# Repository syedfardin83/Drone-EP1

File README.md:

##  LOS (Lark OS):
LOS is a firmware specifically built for the drone flight controller Lark1.

It inludes:
- Reading desired angles/rates from the in-built bluetooth on the ESP32.
- Reading the IMU data (MPU6050).
- Using a complementary filter to obtain the current angles of the drone.
- A PID loop to maintain stability and a smooth flight.

### LOS 1.0
A super loop firmware, with only 1dof control (throttle coontrol only). It was built to test basic tasks like Bluetooth reading, commands string formatting, and motor PWM outputs. It does not include IMU reading and PID calculations.

It is tested and works well.

### LOS 1.1
It was supposed to be complete functional drone superloop firmware with 6dof. But, it did not function, due to some superloop firmware complications.

It is tested and does not work. Hence, moving on to LOS2 which will be FreeRTOS based.

### LOS 2.0
It is a FreeRTOS based complete drone firmware. It has two tasks.
- BT read task
- MPU read + PID calculation

As the Bluetooth task was in the same task in LOS1.1, it was causing the major lag, hence LOS2.0 separates the BT task, while the rest of the tasks are together in another task.

### LOS 2.1
It is an improverment over the LOS 2.0, which now includes 4 tasks.
- BT reading
- IMU reading
- Angles calculation - Complementary filter
- PID loop

LOS 2.1 is more robust, as it uses queues for intertransmission of data between tasks.

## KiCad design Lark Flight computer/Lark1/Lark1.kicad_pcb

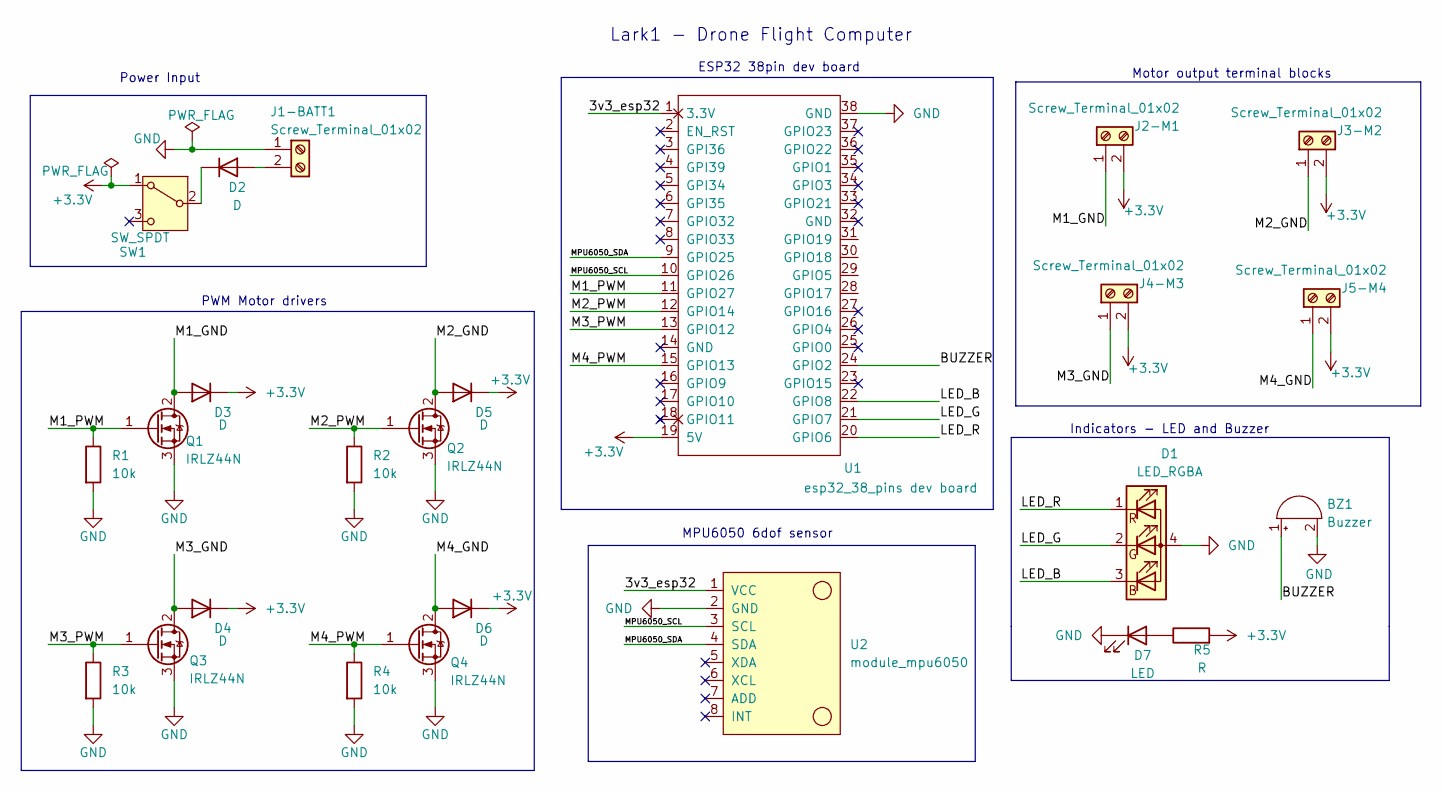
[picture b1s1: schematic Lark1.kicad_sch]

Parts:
BZ1: Buzzer; Buzzer_12x9.5RM7.6
D1: LED_RGBA; LED_D5.0mm-4_RGB_Wide_Pins
D2, D3, D4, D5, D6: D; D_5KPW_P12.70mm_Horizontal
D7: LED; LED_D3.0mm
J1-BATT1, J2-M1, J3-M2, J4-M3, J5-M4: Screw_Terminal_01x02; TerminalBlock_Altech_AK300-2_P5.00mm
Q1, Q2, Q3, Q4: IRLZ44N; TO-220-3_Vertical
R1, R2, R3, R4: 10k; R_Axial_DIN0204_L3.6mm_D1.6mm_P5.08mm_Horizontal
R5: R; R_Axial_DIN0204_L3.6mm_D1.6mm_P5.08mm_Horizontal
SW1: SW_SPDT; SW_Slide_SPDT_Angled_CK_OS102011MA1Q
U1: esp32_38_pins dev board; PinSocket_2x19_P2.54mm_Vertical
U2: module_mpu6050; PinSocket_1x08_P2.54mm_Vertical

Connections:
+3.3V: D3.1 (K), D4.1 (K), D5.1 (K), D6.1 (K), J2-M1.2, J3-M2.2, J4-M3.2, J5-M4.2, R5.2, SW1.1 (A), U1.19 (5V)
/3v3_esp32: U1.1 (3.3V), U2.1 (VCC)
/BUZZER: BZ1.1 (+), U1.24 (GPIO2)
/LED_B: D1.3 (BK), U1.22 (GPIO8)
/LED_G: D1.2 (GK), U1.21 (GPIO7)
/LED_R: D1.1 (RK), U1.20 (GPIO6)
/M1_GND: D3.2 (A), J2-M1.1, Q1.2 (D)
/M1_PWM: Q1.1 (G), R1.1, U1.11 (GPIO27)
/M2_GND: D5.2 (A), J3-M2.1, Q2.2 (D)
/M2_PWM: Q2.1 (G), R2.1, U1.12 (GPIO14)
/M3_GND: D4.2 (A), J4-M3.1, Q3.2 (D)
/M3_PWM: Q3.1 (G), R3.1, U1.13 (GPIO12)
/M4_GND: D6.2 (A), J5-M4.1, Q4.2 (D)
/M4_PWM: Q4.1 (G), R4.1, U1.15 (GPIO13)
/MPU6050_SCL: U1.10 (GPIO26), U2.3 (SCL)
/MPU6050_SDA: U1.9 (GPIO25), U2.4 (SDA)
GND: BZ1.2 (-), D1.4 (A), D7.1 (K), J1-BATT1.1, Q1.3 (S), Q2.3 (S), Q3.3 (S), Q4.3 (S), R1.2, R2.2, R3.2, R4.2, U1.38 (GND), U2.2 (GND)
unnamed: D2.2 (A), J1-BATT1.2
unnamed: D2.1 (K), SW1.2 (B)
unnamed: D7.2 (A), R5.1

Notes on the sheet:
Indicators - LED and Buzzer
PWM Motor drivers
Power Input
MPU6050 6dof sensor
Lark1 - Drone Flight Computer
ESP32 38pin dev board
Motor output terminal blocks

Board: 2 copper layers, 25 parts (0 on the bottom side), 20 nets, no tracks yet.

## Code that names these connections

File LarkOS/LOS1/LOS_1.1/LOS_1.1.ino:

//Lark OS 1.1
// six degrees of freedom (input from joystick)
// Main tasks:
// 1. Take bluetooth input
// 2. Read sensor data
// 3. Run PID

#include "BluetoothSerial.h"
#include <Arduino.h>
#include <Adafruit_MPU6050.h>
#include <Adafruit_Sensor.h>
#include <Wire.h>
#include <math.h>

// Software Objects
BluetoothSerial SerialBT;
Adafruit_MPU6050 mpu;

// Motor pins
int motor_pins[4] = {12,13,14,27};

// Sensor orientation
#define orientation 2

// Indicator Pins
#define LED_R_PIN NULL
#define LED_G_PIN 22
#define LED_B_PIN 23
#define BUZZER_PIN NULL

// MPU6050 pins
#define SCL_PIN 17
#define SDA_PIN 26

// Test button
#define BTN_PIN NULL

// Bluetooth name
#define bt_name "LOS 1.1"

// Serial reading variables
String inputString = "";
bool stringEnd = false;

// Drone control variables
double desiredAngles[3] = {0,0,0};
double throttleIncrement = 0;
double throttle = 0;
double currentAngles[3] = {0,0,0};
double* offsets;
double* data;
double integratedAngles[3] = {0,0,0};
double accAngles[3] = {0,0,0};
double alpha = 0.98;

// Time variables
unsigned long previous_time = 0;
unsigned long current_time = 0;
double dt;

// PID variables
double P=0.09,I=0.01,D=0.01;
double P_terms[3] = {0,0,0};
double I_terms[3] = {0,0,0};
double D_terms[3] = {0,0,0};
double current_errors[3] = {0,0,0};
double previous_errors[3] = {0,0,0};
double rate_outputs[3] = {0,0,0};

// Motor inputs
int motor_inputs[4] = {0,0,0,0};

double* getData(){
  /* Get new sensor events with the readings */
  sensors_event_t a, g, temp;
  mpu.getEvent(&a, &g, &temp);
  static double arr[6];
  arr[0] = a.acceleration.x;
  arr[1] = a.acceleration.y;
  arr[2] = a.acceleration.z;

  arr[3] = g.gyro.x;
  arr[4] = g.gyro.y;
  arr[5] = g.gyro.z;
  return arr;
  // AccX = a.acceleration.x
  // return [a.acceleration.x,a.acceleration.y,a.acceleration.z,a.gyro.x,a.gyro.y,a.gyro.z];
  // double data[6] = {a.acceleration.x, a.acceleration.y, a.acceleration.z, a.gyro.x, a.gyro.y, a.gyro.z};
}

double* getFilteredData(int n){
  double sums[6] = {0,0,0,0,0,0};

  static double avgs[6];

  //Finding sums
  for(int i=1; i<=n; i++){
    static double* data;
    data = getData();
    for(int j=0; j<6; j++){
      sums[j] = sums[j]+data[j];
    }
  }

  //Finding avgs
  for(int i=0; i<6; i++){
    avgs[i] = sums[i]/n;
  }

  return avgs;
}

double* calliberateSensor(){
  static double offsets[6];
  static double* data;
  data = getFilteredData(5);

  for(int i=0; i<6; i++){
    offsets[i] = data[i];
  }

  return offsets;
}

String* splitBySpace(String str){
  static String words[10];int i=0;String word = "";int wordIndex = 0;
  while(i<str.length()){
    if((str[i]==' ')){
      words[wordIndex] = word;
      word="";
      wordIndex++;i++;
      continue;
    }
    if(i==str.length()-1){
      word+=str[i];
      words[wordIndex] = word;break;
    }
    word+=str[i];
    i++;
  }
  return words;
}

void setup() {
  //Initialize all pins
  for(int i=0;i<4;i++){
    pinMode(motor_pins[i],OUTPUT);
  }

  // pinMode(LED_R_PIN,OUTPUT);
  pinMode(LED_G_PIN,OUTPUT);
  pinMode(LED_B_PIN,OUTPUT);
  pinMode(BUZZER_PIN,OUTPUT);

  pinMode(BTN_PIN,INPUT);

  //Initialize Serial
  SerialBT.begin(bt_name);
  Serial.begin(115200);
  delay(100);

  //Initialize MPU6050
  Wire.begin(SDA_PIN,SCL_PIN);
  if (!mpu.begin()) {
    Serial.println("Failed to find MPU6050 chip");
    while (1) {
      delay(10);
    }
  }
  mpu.setAccelerometerRange(MPU6050_RANGE_16_G);
  mpu.setGyroRange(MPU6050_RANGE_250_DEG);
  mpu.setFilterBandwidth(MPU6050_BAND_21_HZ);
  delay(100);

  //Calliberate sensor
  offsets = calliberateSensor();
}

void loop() {

  //Bluetooth read
  if(SerialBT.available()){
    char ch = SerialBT.read();
    if (ch == '\n') {
      stringEnd = true;
    } else {
      inputString += ch;
    }
  }
  if(stringEnd){
        inputString.trim();
        if(inputString=="STOP"){
          Serial.println("Emergency stop protocol initiated !!!");
          for(int i=0;i<4;i++){
            analogWrite(motor_pins[i],0);
          }
          while(1){

          }
        }
        Serial.println(inputString);
        String* command = splitBySpace(inputString);

        //Update desired angles
        for(int i=0;i<3;i++){
          desiredAngles[i] = radians(command[i].toDouble());
        }
        throttleIncrement = command[3].toDouble();
        throttle+=throttleIncrement;
        throttleIncrement = 0;

        inputString = "";
        stringEnd = false;

        // Serial.print(throttle);
        // Serial.print("  ");
        // for(int i=0;i<3;i++){
        //   Serial.print(desiredAngles[i]);
        //   Serial.print("  ");
        }
        // Serial.println("");


  // Read Sensor data
    // current_time = micros();
    // data = getFilteredData(5);


    // // Calculate angles
    // dt = (current_time-previous_time)*pow(10,-6);
    // //Integrated Angles
    // for(int i=0;i<3;i++){
    //   integratedAngles[i]+=dt*(data[i+3]-offsets[i+3]);
    // }

    // //Angles from triginometry/Acceletration
    // if(orientation == 2){
    //   if(data[0]==0){
    //     accAngles[1] = 3.14/2;
    //     accAngles[2] = 3.14/2;
    //   }else{
    //         accAngles[2] = atan(data[1]/data[0]);
    //         accAngles[1] = atan(data[2]/data[0]);
    //   }
    // }
    // //Sign correction
    // if(orientation==2){
    //   // double temp=integratedAngles[0];
    //   accAngles[2] = -accAngles[2];
    //   // integratedAngles[0] = -temp;
    // }
    // // accAngles[0] = integratedAngles[0];
    // // //Complementary filter
    // for(int i=1; i<3; i++){
    //   currentAngles[i] = alpha*integratedAngles[i] + (1-alpha)*accAngles[i];
    // }
    // currentAngles[0] = integratedAngles[0];

    // // PID control


    // // Finding errors in angles
    // for(int i =0;i<3;i++){
    //   current_errors[i] = currentAngles[i]-desiredAngles[i];
    // }

    // // // Find rate outputs:
    // for(int i=0;i<3;i++){
    //   P_terms[i] = P*current_errors[i];
    //   I_terms[i] = I_terms[i]+I*current_errors[i]*dt;
    //   D_terms[i] = (current_errors[i]-previous_errors[i])/dt;

    //   rate_outputs[i] = P_terms[i];
    // }
    // //calculate motor inputs
    // motor_inputs[0] = (throttle-rate_outputs[0]-rate_outputs[1]+rate_outputs[2])*255;
    // motor_inputs[1] = (throttle-rate_outputs[0]+rate_outputs[1]-rate_outputs[2])*255;
    // motor_inputs[2] = (throttle+rate_outputs[0]+rate_outputs[1]+rate_outputs[2])*255;
    // motor_inputs[3] = (throttle+rate_outputs[0]-rate_outputs[1]-rate_outputs[2])*255;

    // //Give motor inputs
    // for(int i=0;i<4;i++){
    //   if(motor_inputs[i]<0){
    //     motor_inputs[i] = 0;
    //   }
    //   else if(motor_inputs[i]>255){
    //     motor_inputs[i] = 255;
    //   }
    // }

    // for(int i=0;i<3;i++){

    //   previous_errors[i] = current_errors[i];
    // }
    // previous_time = current_time;
}

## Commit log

2025-05-21 Images added
2025-05-21 CGPT generated basic data gui frontend
2025-05-21 String manipulation of mpu data python
2025-05-21 GUI ready to show data
2025-05-23 moved images
2025-05-27 notes from one note
2025-05-27 mpu6050 mouse
2025-05-27 Mouse 1, I think we should drop the idea of virtual space
2025-05-28 GUI 2 v1
2025-05-28 GUI 2 v2
2025-05-28 GUI 2 v3
2025-05-28 GUI 2 serial bug not fixed yet
2025-05-28 GUI 2 over and out. Will work on my own Dashboard GUI.
2025-05-29 GUI 3 - My own. Only one graph present with high latency. OOP approach.
2025-05-29 GUI 3 latency lowered - just created more threads.
2025-05-30 GUI4 - a mixture of CGPT and my code.
2025-06-03 Acc method(in compFilter.py) and Gyro method(in virtualSpaceGyro.py) ready, next step is to combine them.
2025-06-03 tkVisualization of Pitch angle using acc and gyro, next step make complementary filter
2025-06-03 CompFilter is complete in tkVisualize.py with clean code, along with a video demonstration.
2025-06-04 Started LED PID Coding
2025-06-05 Platform IO started and written basic Gyro code in c++
2025-06-06 PID coding done, P,I,D constants not found yet.
2025-06-06 video demonstration of led pid simulator
2025-06-06 Nothing much
2025-06-13 Recorded values of PWM and MOSFET plus LED
2025-06-24 Motor driver done(Check images and videos)
2025-06-24 Motor driver Schematic in kicad done
2025-06-30 Serial communication learning
2025-07-05 HC-05 finally works!!!!
2025-07-05 HC05 string reading done
2025-07-07 PID Python UI done
2025-07-08 backup
2025-07-09 Trying from other laptop
2025-07-13 test commit
2025-07-13 test commit 2
2025-07-13 Lark1 Flight computer power input schematic kicad done
2025-07-14 ESP32 mpu6050
2025-07-14 Lark1 almost done, indicators left
2025-07-14 Lark1 1.0
2025-07-14 Lark1 1.0 Schematic pdf added
2025-07-14 Lark1 refining
2025-07-14 Lark1 Kicad ERC check - no errors
2025-07-18 LarkOS1 started
2025-07-18 LOS1 completed - very very basic
2025-07-18 Complementary filter in esp32
2025-07-18 LOS 1.1 till calculating angles by integration. Next, calculate angles by acc method.
2025-07-18 LOS 1.1 code completed. Good luck testing it!! ;)
2025-07-18 LOS 1.1 Minor Improvements
2025-07-19 LOS 1.1 DONE!! PID works fine.
2025-07-19 LOS 1.1 minor bug fixes
2025-07-19 LOS 1.1 z-axis rotation remaining, rest all is good. Next up, make drone body and BT transmission from laptop
2025-07-19 LOS 1.1 minor fixes
2025-07-19 First xbox transmission through PC works!!
2025-07-19 LOS 1.1 Bug fixes
2025-07-23 LARK1 motor pinouts
2025-07-26 LOS1 - thrust only control in ESP32/Bluetooth
2025-07-27 Android Lark1 controller in flutter by Cursor AI
2025-07-29 LOS2 Bluetooth reading and updating done!
2025-08-04 LOS2 mpu read task, bluetooth.ino
2025-08-04 LOS2 - comp filter untested
2025-08-04 LOS2 PID - untested; LOS2 done?
2025-08-14 LOS2.1 started; 3 separate tasks - dt1 and dt2; Using Queues for safer data sharing
2025-08-15 LOS2.1 - completed till mpu task; Not Tested;
2025-08-15 calculate_angles_task done; PID task - from calculating dt; ToDo pending;
2025-08-15 All tasks done; Not satisfied with dt2 calculation; toDO pending;
